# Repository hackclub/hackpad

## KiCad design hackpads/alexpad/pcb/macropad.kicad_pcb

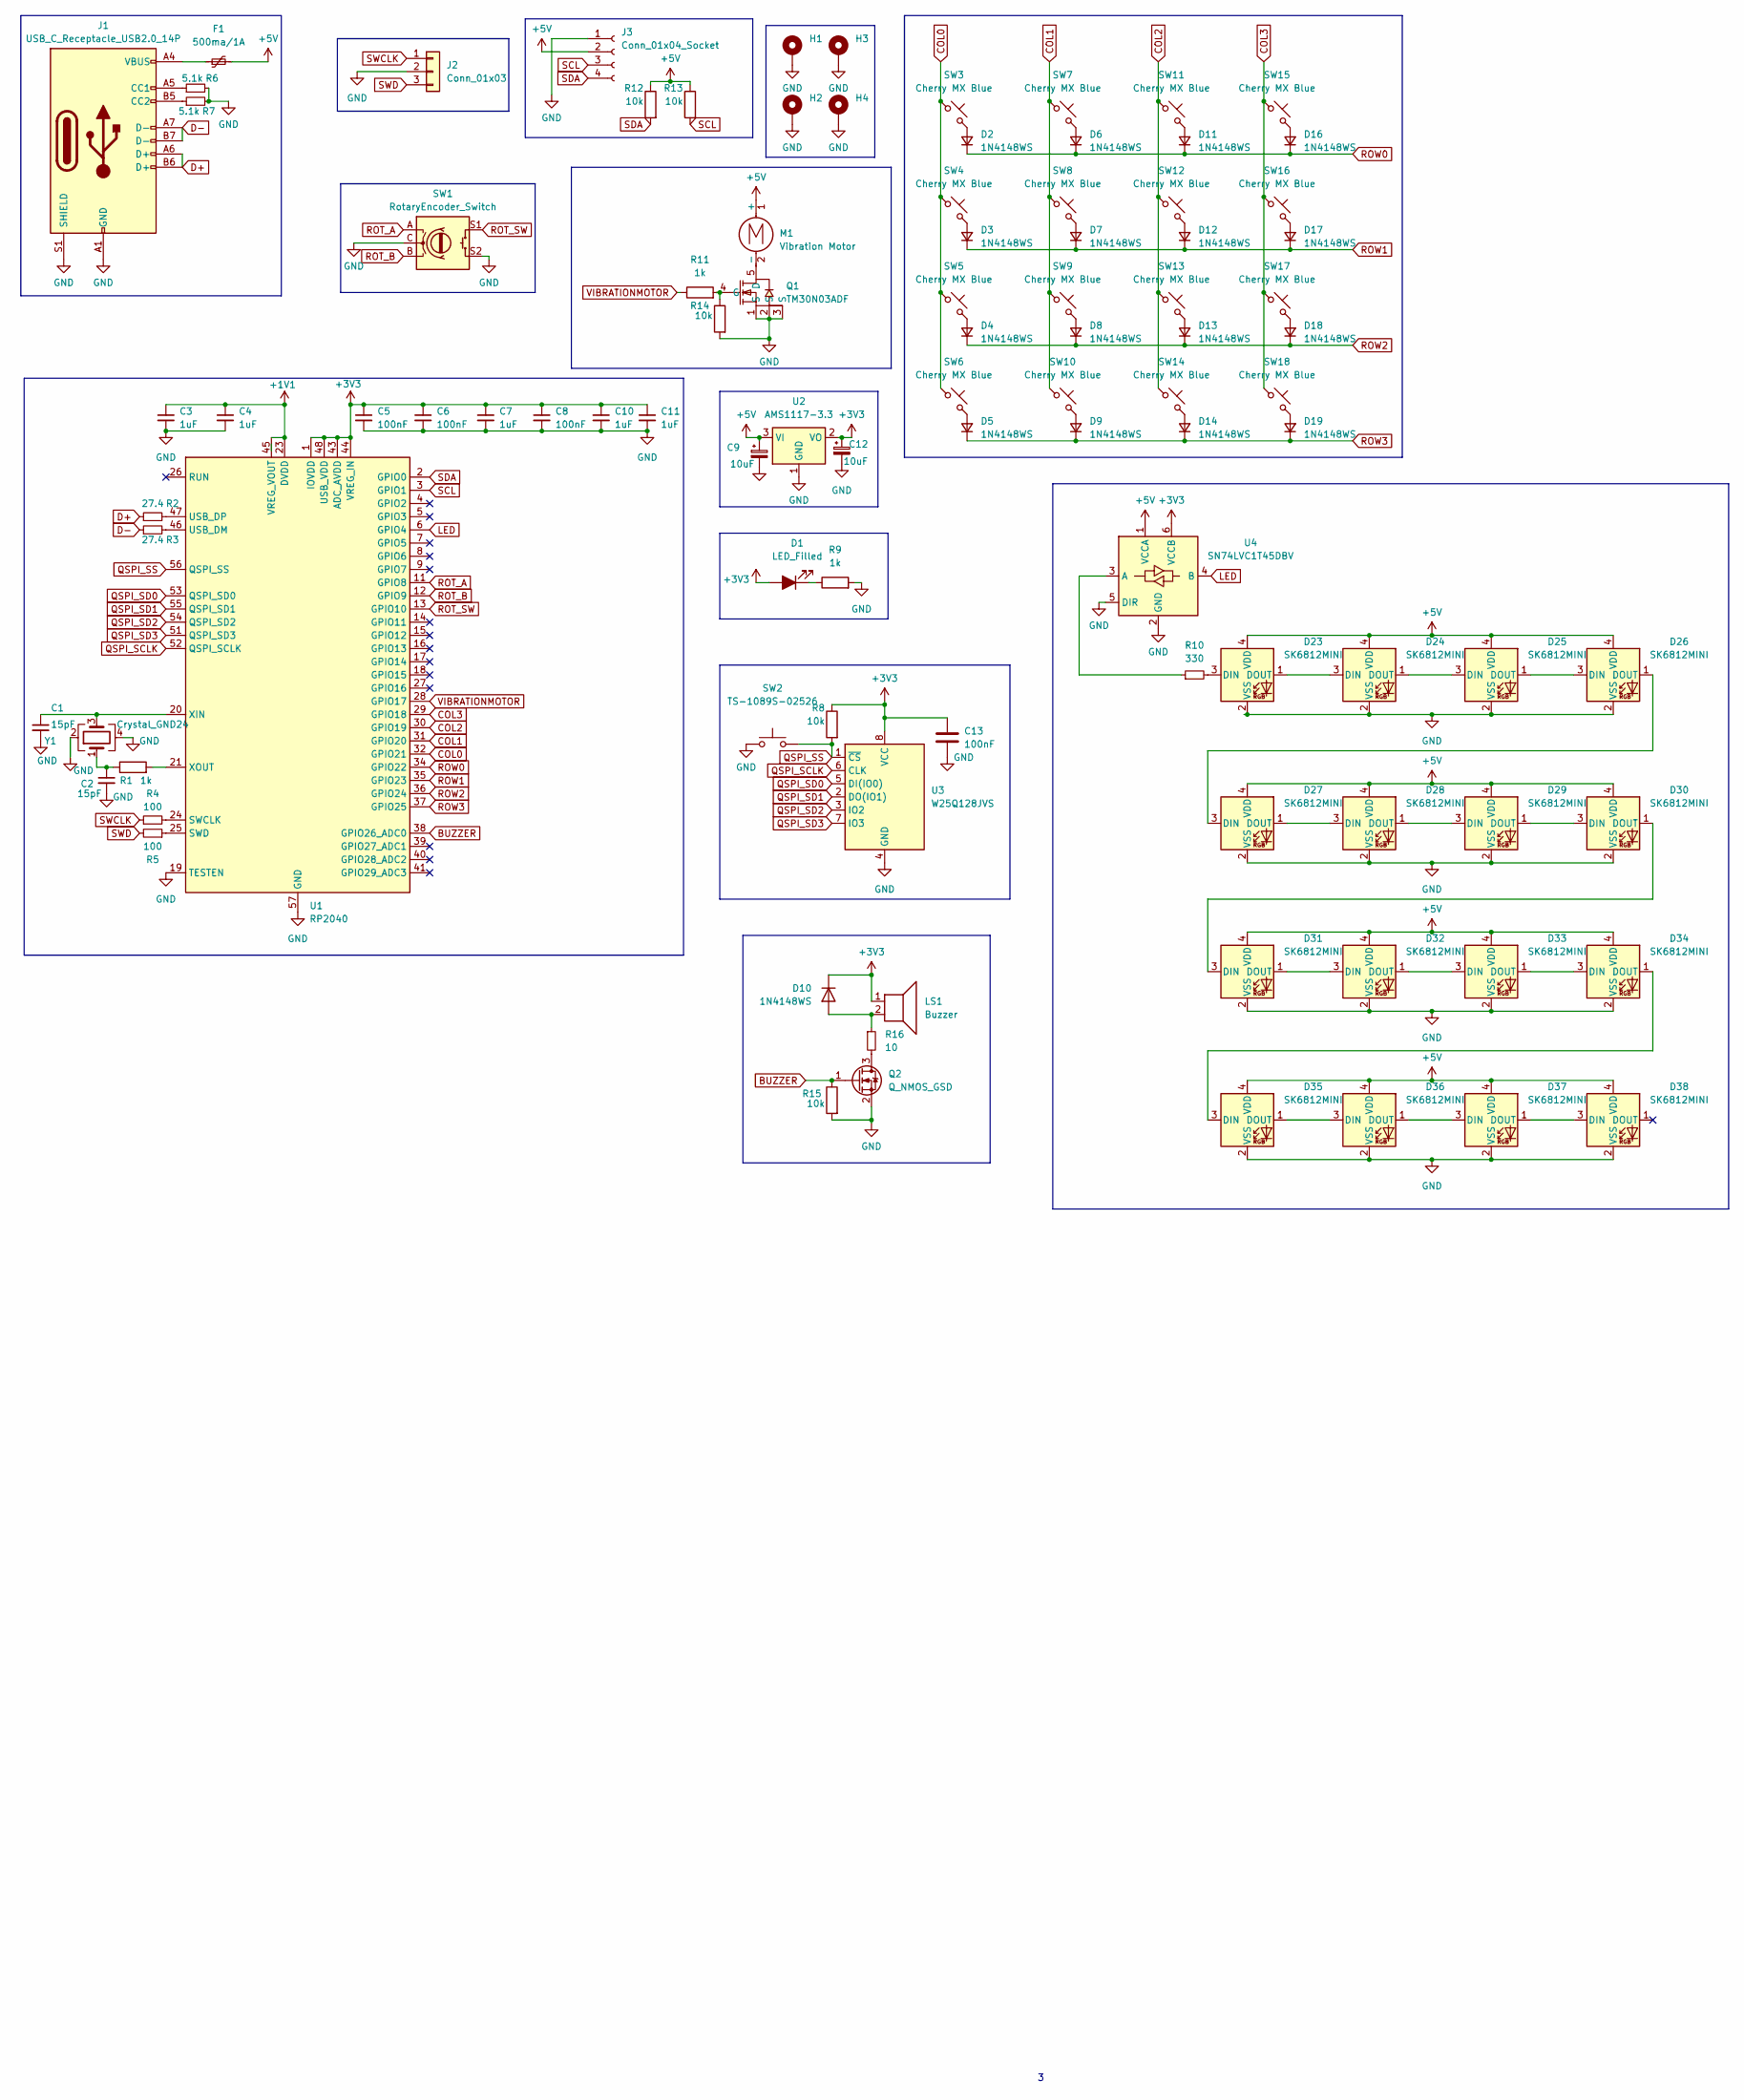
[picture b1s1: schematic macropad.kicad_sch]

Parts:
C1, C2: 15pF; C_0402_1005Metric; LCSC Part C1548
C3, C4, C7, C10, C11: 1uF; C_0402_1005Metric; LCSC Part C52923
C5, C6, C8, C13: 100nF; C_0402_1005Metric; LCSC Part C1525
C9, C12: 10uF; C_1206_3216Metric; LCSC Part C7171
D1: LED_Filled; LED_0603_1608Metric; LCSC Part C2286
D2, D3, D4, D5, D6, D7, D8, D9, D11, D12, D13, D14, D16, D17, D18, D19: 1N4148WS; D_SOD-323F; LCSC Part C917117
D10: 1N4148WS; D_SOD-323; LCSC Part C2828422
D23, D24, D25, D26, D27, D28, D29, D30, D31, D32, D33, D34, D35, D36, D37, D38: SK6812MINI; SK6812MINI-E; LCSC Part C5149201
F1: 500ma/1A; Fuse_1206_3216Metric_Pad1.42x1.75mm_HandSolder; LCSC Part C720075
H1, H2, H3, H4: MountingHole_Pad; MountingHole_2.2mm_M2_DIN965_Pad
J1: USB_C_Receptacle_USB2.0_14P; USB_C_Receptacle_G-Switch_GT-USB-7010ASV; LCSC Part C2988369
J2: Conn_01x03; JST_SH_BM03B-SRSS-TB_1x03-1MP_P1.00mm_Vertical; LCSC Part C160389
J3: Conn_01x04_Socket; OLED-TH_L38.0-W12.0_HS91L02W2C01; LCSC Part C5248081
LS1: Buzzer; BUZ-SMD_4P-L8.5-W8.5-P8.50-BR; LCSC Part C94599
M1: Vibration Motor; PinHeader_1x02_P2.54mm_Vertical
Q1: TM30N03ADF; WDFN-5_L3.3-W3.3-P0.65-BL; LCSC Part C7422839
Q2: Q_NMOS_GSD; SOT-23_Handsoldering; LCSC Part C347475
R1, R9, R11: 1k; R_0402_1005Metric; LCSC Part C11702
R2, R3: 27.4; R_0603_1608Metric; LCSC Part C5126244
R4, R5: 100; R_0603_1608Metric_Pad0.98x0.95mm_HandSolder; LCSC Part C7250
R6, R7: 5.1k; R_0603_1608Metric_Pad0.98x0.95mm_HandSolder; LCSC Part C23186
R8, R12, R13, R14, R15: 10k; R_0805_2012Metric; LCSC Part C17414
R10: 330; R_0603_1608Metric_Pad0.98x0.95mm_HandSolder; LCSC Part C23138
R16: 10; R_0603_1608Metric_Pad0.98x0.95mm_HandSolder; LCSC Part C22859
SW1: RotaryEncoder_Switch; SW-TH_EC11XXXXXXXX; LCSC Part C470742
SW2: TS-1089S-02526; SW-SMD_4P-L4.2-W3.3-P2.15-LS5.1; LCSC Part C455282
SW3, SW4, SW5, SW6, SW7, SW8, SW9, SW10, SW11, SW12, SW13, SW14, SW15, SW16, SW17, SW18: Cherry MX Blue; SW_Cherry_MX_PCB_1.00u
U1: RP2040; QFN-56-1EP_7x7mm_P0.4mm_EP3.2x3.2mm; LCSC Part C2040
U2: AMS1117-3.3; SOT-223-3_TabPin2; LCSC Part C6186
U3: W25Q128JVS; SOIC-8_5.23x5.23mm_P1.27mm; LCSC Part C97521
U4: SN74LVC1T45DBV; SOT-23-6; LCSC Part C7843
Y1: Crystal_GND24; Crystal_SMD_3225-4Pin_3.2x2.5mm; LCSC Part C20625731

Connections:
+1V1: C3.1, C4.1, U1.23 (DVDD), U1.45 (VREG_VOUT), U1.50 (DVDD)
+3V3: C5.1, C6.1, C7.1, C8.1, C10.1, C11.1, C12.1, C13.1, D1.2 (A), D10.1 (K), LS1.1, R8.1, U1.1 (IOVDD), U1.10 (IOVDD), U1.22 (IOVDD), U1.33 (IOVDD), U1.42 (IOVDD), U1.43 (ADC_AVDD), U1.44 (VREG_IN), U1.48 (USB_VDD), U1.49 (IOVDD), U2.2 (VO), U3.8 (VCC), U4.6 (VCCB)
+5V: C9.1, D23.4 (VDD), D24.4 (VDD), D25.4 (VDD), D26.4 (VDD), D27.4 (VDD), D28.4 (VDD), D29.4 (VDD), D30.4 (VDD), D31.4 (VDD), D32.4 (VDD), D33.4 (VDD), D34.4 (VDD), D35.4 (VDD), D36.4 (VDD), D37.4 (VDD), D38.4 (VDD), F1.2, J3.2, M1.1 (+), R12.1, R13.1, U2.3 (VI), U4.1 (VCCA)
BUZZER: Q2.1 (G), R15.1, U1.38 (GPIO26_ADC0)
COL0: SW3.1, SW4.1, SW5.1, SW6.1, U1.32 (GPIO21)
COL1: SW7.1, SW8.1, SW9.1, SW10.1, U1.31 (GPIO20)
COL2: SW11.1, SW12.1, SW13.1, SW14.1, U1.30 (GPIO19)
COL3: SW15.1, SW16.1, SW17.1, SW18.1, U1.29 (GPIO18)
D+: J1.A6 (D+), J1.B6 (D+), R2.1
D-: J1.A7 (D-), J1.B7 (D-), R3.1
GND: C1.2, C2.2, C3.2, C4.2, C5.2, C6.2, C7.2, C8.2, C9.2, C10.2, C11.2, C12.2, C13.2, D23.2 (VSS), D24.2 (VSS), D25.2 (VSS), D26.2 (VSS), D27.2 (VSS), D28.2 (VSS), D29.2 (VSS), D30.2 (VSS), D31.2 (VSS), D32.2 (VSS), D33.2 (VSS), D34.2 (VSS), D35.2 (VSS), D36.2 (VSS), D37.2 (VSS), D38.2 (VSS), H1.1, H2.1, H3.1, H4.1, J1.A1 (GND), J1.A12 (GND), J1.B1 (GND), J1.B12 (GND), J1.S1 (SHIELD), J2.2, J3.1, Q1.1 (S), Q1.2 (S), Q1.3 (S), Q2.2 (S), R6.2, R7.2, R9.2, R14.2, R15.2, SW1.C, SW1.S2, SW2.1, U1.19 (TESTEN), U1.57 (GND), U2.1 (GND), U3.4 (GND), U4.2 (GND), U4.5 (DIR), Y1.2, Y1.4
LED: U1.6 (GPIO4), U4.4 (B)
unnamed: C2.1, R1.1, Y1.1
unnamed: D1.1 (K), R9.1
unnamed: D2.2 (A), SW3.2
unnamed: D3.2 (A), SW4.2
unnamed: D4.2 (A), SW5.2
unnamed: D5.2 (A), SW6.2
unnamed: D6.2 (A), SW7.2
unnamed: D7.2 (A), SW8.2
unnamed: D8.2 (A), SW9.2
unnamed: D9.2 (A), SW10.2
unnamed: D10.2 (A), LS1.2, R16.1
unnamed: D11.2 (A), SW11.2
unnamed: D12.2 (A), SW12.2
unnamed: D13.2 (A), SW13.2
unnamed: D14.2 (A), SW14.2
unnamed: D16.2 (A), SW15.2
unnamed: D17.2 (A), SW16.2
unnamed: D18.2 (A), SW17.2
unnamed: D19.2 (A), SW18.2
unnamed: D23.3 (DIN), R10.2
unnamed: D23.1 (DOUT), D24.3 (DIN)
unnamed: D24.1 (DOUT), D25.3 (DIN)
unnamed: D25.1 (DOUT), D26.3 (DIN)
unnamed: D26.1 (DOUT), D27.3 (DIN)
unnamed: D27.1 (DOUT), D28.3 (DIN)
unnamed: D28.1 (DOUT), D29.3 (DIN)
unnamed: D29.1 (DOUT), D30.3 (DIN)
unnamed: D30.1 (DOUT), D31.3 (DIN)
unnamed: D31.1 (DOUT), D32.3 (DIN)
unnamed: D32.1 (DOUT), D33.3 (DIN)
unnamed: D33.1 (DOUT), D34.3 (DIN)
unnamed: D34.1 (DOUT), D35.3 (DIN)
unnamed: D35.1 (DOUT), D36.3 (DIN)
unnamed: D36.1 (DOUT), D37.3 (DIN)
unnamed: D37.1 (DOUT), D38.3 (DIN)
unnamed: F1.1, J1.A4 (VBUS), J1.A9 (VBUS), J1.B4 (VBUS), J1.B9 (VBUS)
unnamed: J1.A5 (CC1), R6.1
unnamed: J1.B5 (CC2), R7.1
unnamed: M1.2 (-), Q1.5 (D)
unnamed: Q1.4 (G), R11.2, R14.1
unnamed: Q2.3 (D), R16.2
unnamed: R4.2, U1.24 (SWCLK)
unnamed: R5.1, U1.25 (SWD)
unnamed: R3.2, U1.46 (USB_DM)
unnamed: R2.2, U1.47 (USB_DP)
unnamed: C1.1, U1.20 (XIN), Y1.3
unnamed: R1.2, U1.21 (XOUT)
unnamed: R10.1, U4.3 (A)
QSPI_SCLK: U1.52 (QSPI_SCLK), U3.6 (CLK)
QSPI_SD0: U1.53 (QSPI_SD0), U3.5 (DI(IO0))
QSPI_SD1: U1.55 (QSPI_SD1), U3.2 (DO(IO1))
QSPI_SD2: U1.54 (QSPI_SD2), U3.3 (IO2)
QSPI_SD3: U1.51 (QSPI_SD3), U3.7 (IO3)
QSPI_SS: R8.2, SW2.2, U1.56 (QSPI_SS), U3.1 (~CS)
ROT_A: SW1.A, U1.11 (GPIO8)
ROT_B: SW1.B, U1.12 (GPIO9)
ROT_SW: SW1.S1, U1.13 (GPIO10)
ROW0: D2.1 (K), D6.1 (K), D11.1 (K), D16.1 (K), U1.34 (GPIO22)
ROW1: D3.1 (K), D7.1 (K), D12.1 (K), D17.1 (K), U1.35 (GPIO23)
ROW2: D4.1 (K), D8.1 (K), D13.1 (K), D18.1 (K), U1.36 (GPIO24)
ROW3: D5.1 (K), D9.1 (K), D14.1 (K), D19.1 (K), U1.37 (GPIO25)
SCL: J3.3, R13.2, U1.3 (GPIO1)
SDA: J3.4, R12.2, U1.2 (GPIO0)
SWCLK: J2.1, R4.1
SWD: J2.3, R5.2
VIBRATIONMOTOR: R11.1, U1.28 (GPIO17)

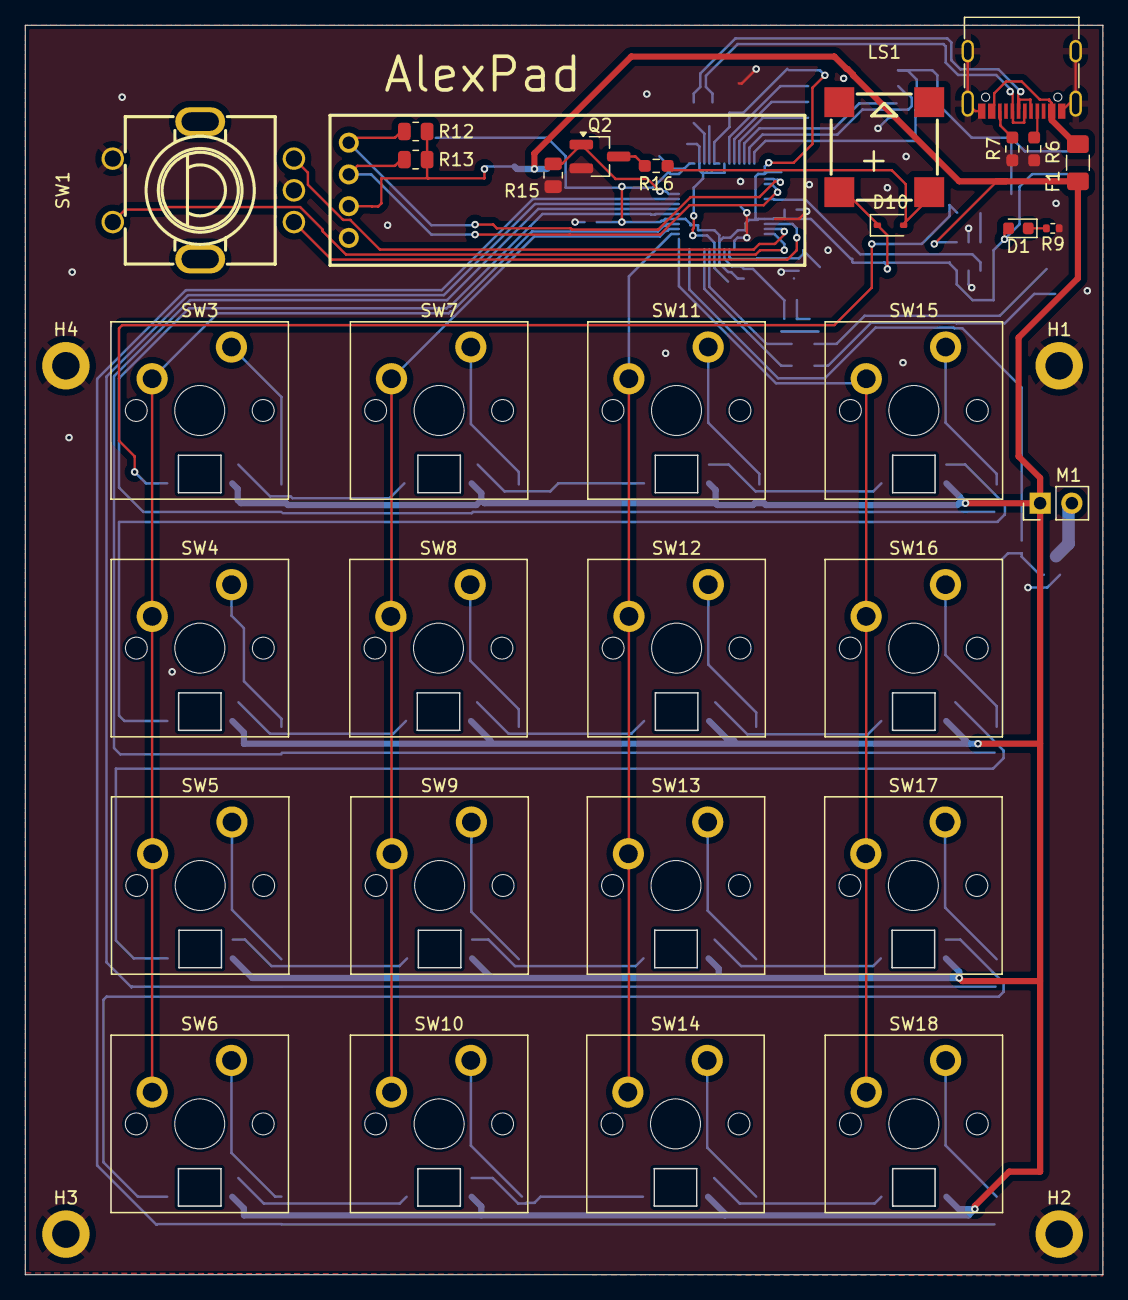
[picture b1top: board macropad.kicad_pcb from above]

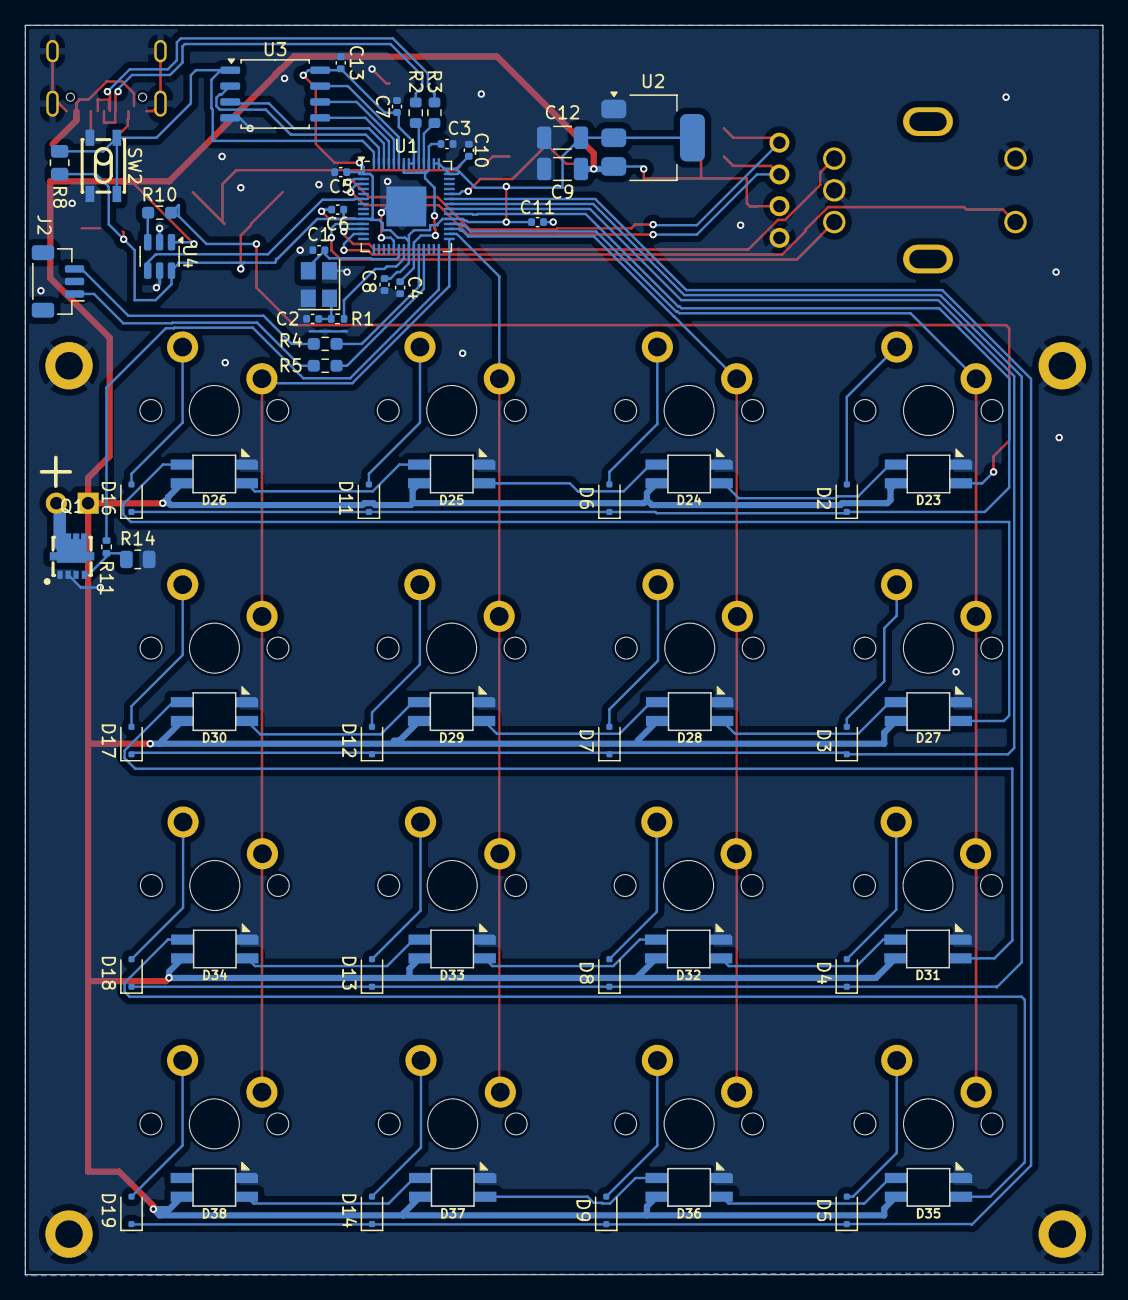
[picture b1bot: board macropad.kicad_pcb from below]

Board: 2 copper layers, 86.2 x 100.0 mm, 98 parts (62 on the bottom side), 78 nets.

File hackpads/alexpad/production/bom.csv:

"Reference","Qty","Value","Footprint","LCSC Part"
"C1,C2","2","15pF","Capacitor_SMD:C_0402_1005Metric","C1548"
"C5,C6,C8,C13","4","100nF","Capacitor_SMD:C_0402_1005Metric","C1525"
"C3,C4,C7,C10,C11","5","1uF","Capacitor_SMD:C_0402_1005Metric","C52923"
"C9,C12","2","10uF","Capacitor_SMD:C_1206_3216Metric","C7171"
"R2,R3","2","27.4","Resistor_SMD:R_0603_1608Metric","C5126244"
"R4,R5","2","100","Resistor_SMD:R_0603_1608Metric_Pad0.98x0.95mm_HandSolder"," C7250"
"R10","1","330","Resistor_SMD:R_0603_1608Metric_Pad0.98x0.95mm_HandSolder","C23138"
"R1,R9,R11","3","1k","Resistor_SMD:R_0402_1005Metric","C11702"
"R6,R7","2","5.1k","Resistor_SMD:R_0603_1608Metric_Pad0.98x0.95mm_HandSolder","C23186"
"R8,R12,R13,R14","4","10k","Resistor_SMD:R_0805_2012Metric"," C17414"
"D2,D3,D4,D5,D6,D7,D8,D9,D11,D12,D13,D14,D16,D17,D18,D19","16","1N4148WS","Diode_SMD:D_SOD-323F","C917117"
"F1","1","500ma/1A","Fuse:Fuse_1206_3216Metric_Pad1.42x1.75mm_HandSolder","C720075"
"U2","1","AMS1117-3.3","Package_TO_SOT_SMD:SOT-223-3_TabPin2","C6186"
"SW3,SW4,SW5,SW6,SW7,SW8,SW9,SW10,SW11,SW12,SW13,SW14,SW15,SW16,SW17,SW18","16","Cherry MX Blue","PCM_Switch_Keyboard_Cherry_MX:SW_Cherry_MX_PCB_1.00u",""
"J2","1","Conn_01x03","Connector_JST:JST_SH_BM03B-SRSS-TB_1x03-1MP_P1.00mm_Vertical","C160389"
"J3","1","Conn_01x04_Socket","easyeda2kicad:OLED-TH_L38.0-W12.0_HS91L02W2C01","C5248081"
"Y1","1","Crystal_GND24","Crystal:Crystal_SMD_3225-4Pin_3.2x2.5mm","C20625731"
"D1","1","LED_Filled","LED_SMD:LED_0603_1608Metric","C2286"
"H1,H2,H3,H4","4","MountingHole_Pad","MountingHole:MountingHole_2.2mm_M2_DIN965_Pad",""
"SW1","1","RotaryEncoder_Switch","easyeda2kicad:SW-TH_EC11XXXXXXXX","C470742"
"U1","1","RP2040","Package_DFN_QFN:QFN-56-1EP_7x7mm_P0.4mm_EP3.2x3.2mm","C2040"
"D23,D24,D25,D26,D27,D28,D29,D30,D31,D32,D33,D34,D35,D36,D37,D38","16","SK6812MINI","cheyao macropad main PCB-third_party_neopixel.petty:SK6812MINI-E","C5149201"
"U4","1","SN74LVC1T45DBV","Package_TO_SOT_SMD:SOT-23-6","C7843"
"Q1","1","TM30N03ADF","easyeda2kicad:WDFN-5_L3.3-W3.3-P0.65-BL","C7422839"
"SW2","1","TS-1089S-02526","easyeda2kicad:SW-SMD_4P-L4.2-W3.3-P2.15-LS5.1","C455282"
"J1","1","USB_C_Receptacle_USB2.0_14P","Connector_USB:USB_C_Receptacle_G-Switch_GT-USB-7010ASV","C2988369"
"M1","1","Vibration Motor","Connector_PinHeader_2.54mm:PinHeader_1x02_P2.54mm_Vertical",""
"U3","1","W25Q128JVS","Package_SO:SOIC-8_5.23x5.23mm_P1.27mm","C97521"

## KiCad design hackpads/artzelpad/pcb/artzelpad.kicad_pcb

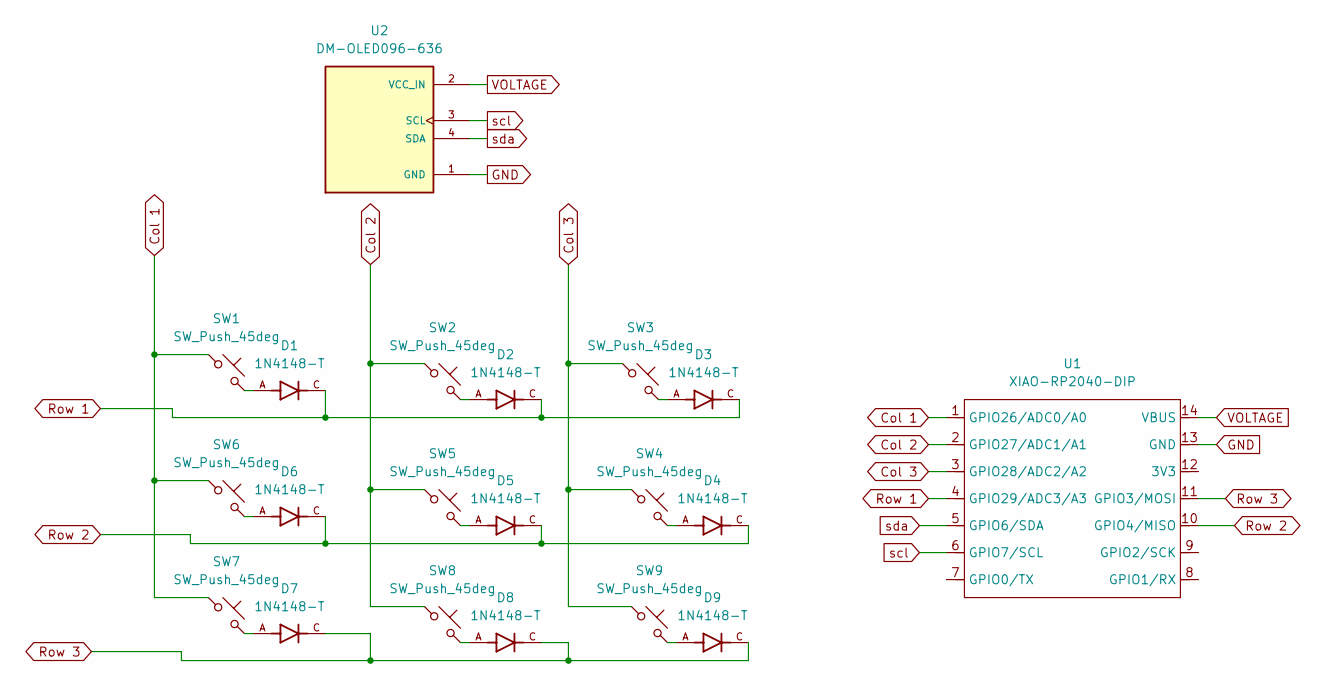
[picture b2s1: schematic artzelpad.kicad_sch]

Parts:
D1, D2, D3, D4, D5, D6, D7, D8, D9: 1N4148-T; DIOAD820W60L400D200; PARTREV 9-3
SW1, SW2, SW3, SW4, SW5, SW6, SW7, SW8, SW9: SW_Push_45deg; SW_Cherry_MX_1.00u_PCB_3D_model
U1: XIAO-RP2040-DIP; XIAO-RP2040-DIP_1
U2: DM-OLED096-636; SSD1306-0.91-OLED-4pin-128x32; PARTREV 2018-09-10

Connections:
Col 1: SW1.1, SW6.1, SW7.1, U1.1 (GPIO26/ADC0/A0)
Col 2: SW2.1, SW5.1, SW8.1, U1.2 (GPIO27/ADC1/A1)
Col 3: SW3.1, SW4.1, SW9.1, U1.3 (GPIO28/ADC2/A2)
GND: U1.13 (GND), U2.1 (GND)
unnamed: D1.A, SW1.2
unnamed: D2.A, SW2.2
unnamed: D3.A, SW3.2
unnamed: D4.A, SW4.2
unnamed: D5.A, SW5.2
unnamed: D6.A, SW6.2
unnamed: D7.A, SW7.2
unnamed: D8.A, SW8.2
unnamed: D9.A, SW9.2
Row 1: D1.C, D2.C, D3.C, U1.4 (GPIO29/ADC3/A3)
Row 2: D4.C, D5.C, D6.C, U1.10 (GPIO4/MISO)
Row 3: D7.C, D8.C, D9.C, U1.11 (GPIO3/MOSI)
VOLTAGE: U1.14 (VBUS), U2.2 (VCC_IN)
scl: U1.6 (GPIO7/SCL), U2.3 (SCL)
sda: U1.5 (GPIO6/SDA), U2.4 (SDA)

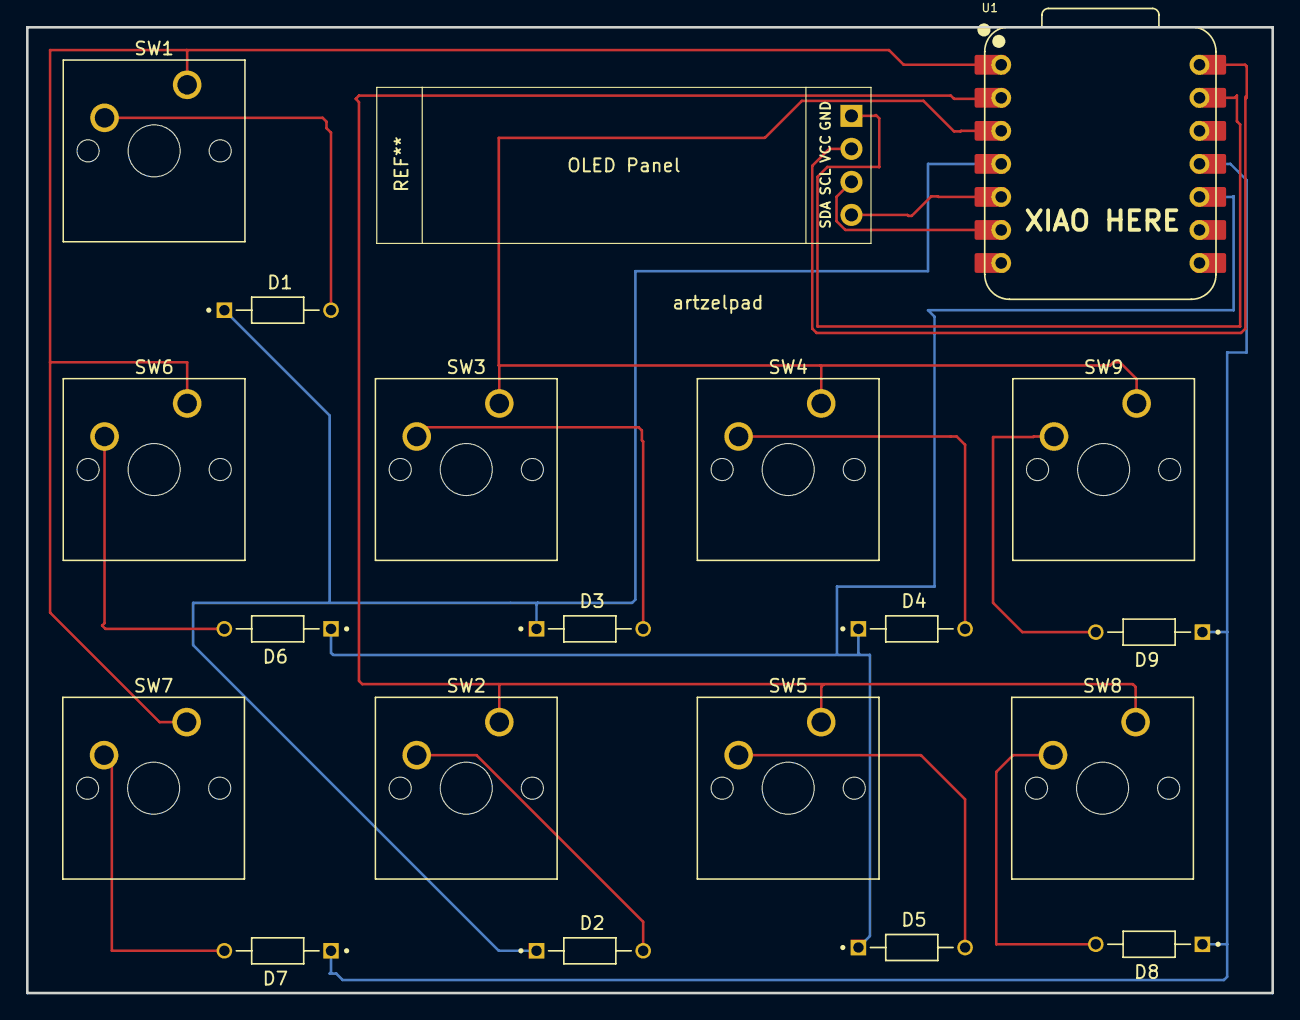
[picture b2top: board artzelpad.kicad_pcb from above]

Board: 2 copper layers, 95.8 x 74.2 mm, 19 parts (0 on the bottom side), 15 nets.

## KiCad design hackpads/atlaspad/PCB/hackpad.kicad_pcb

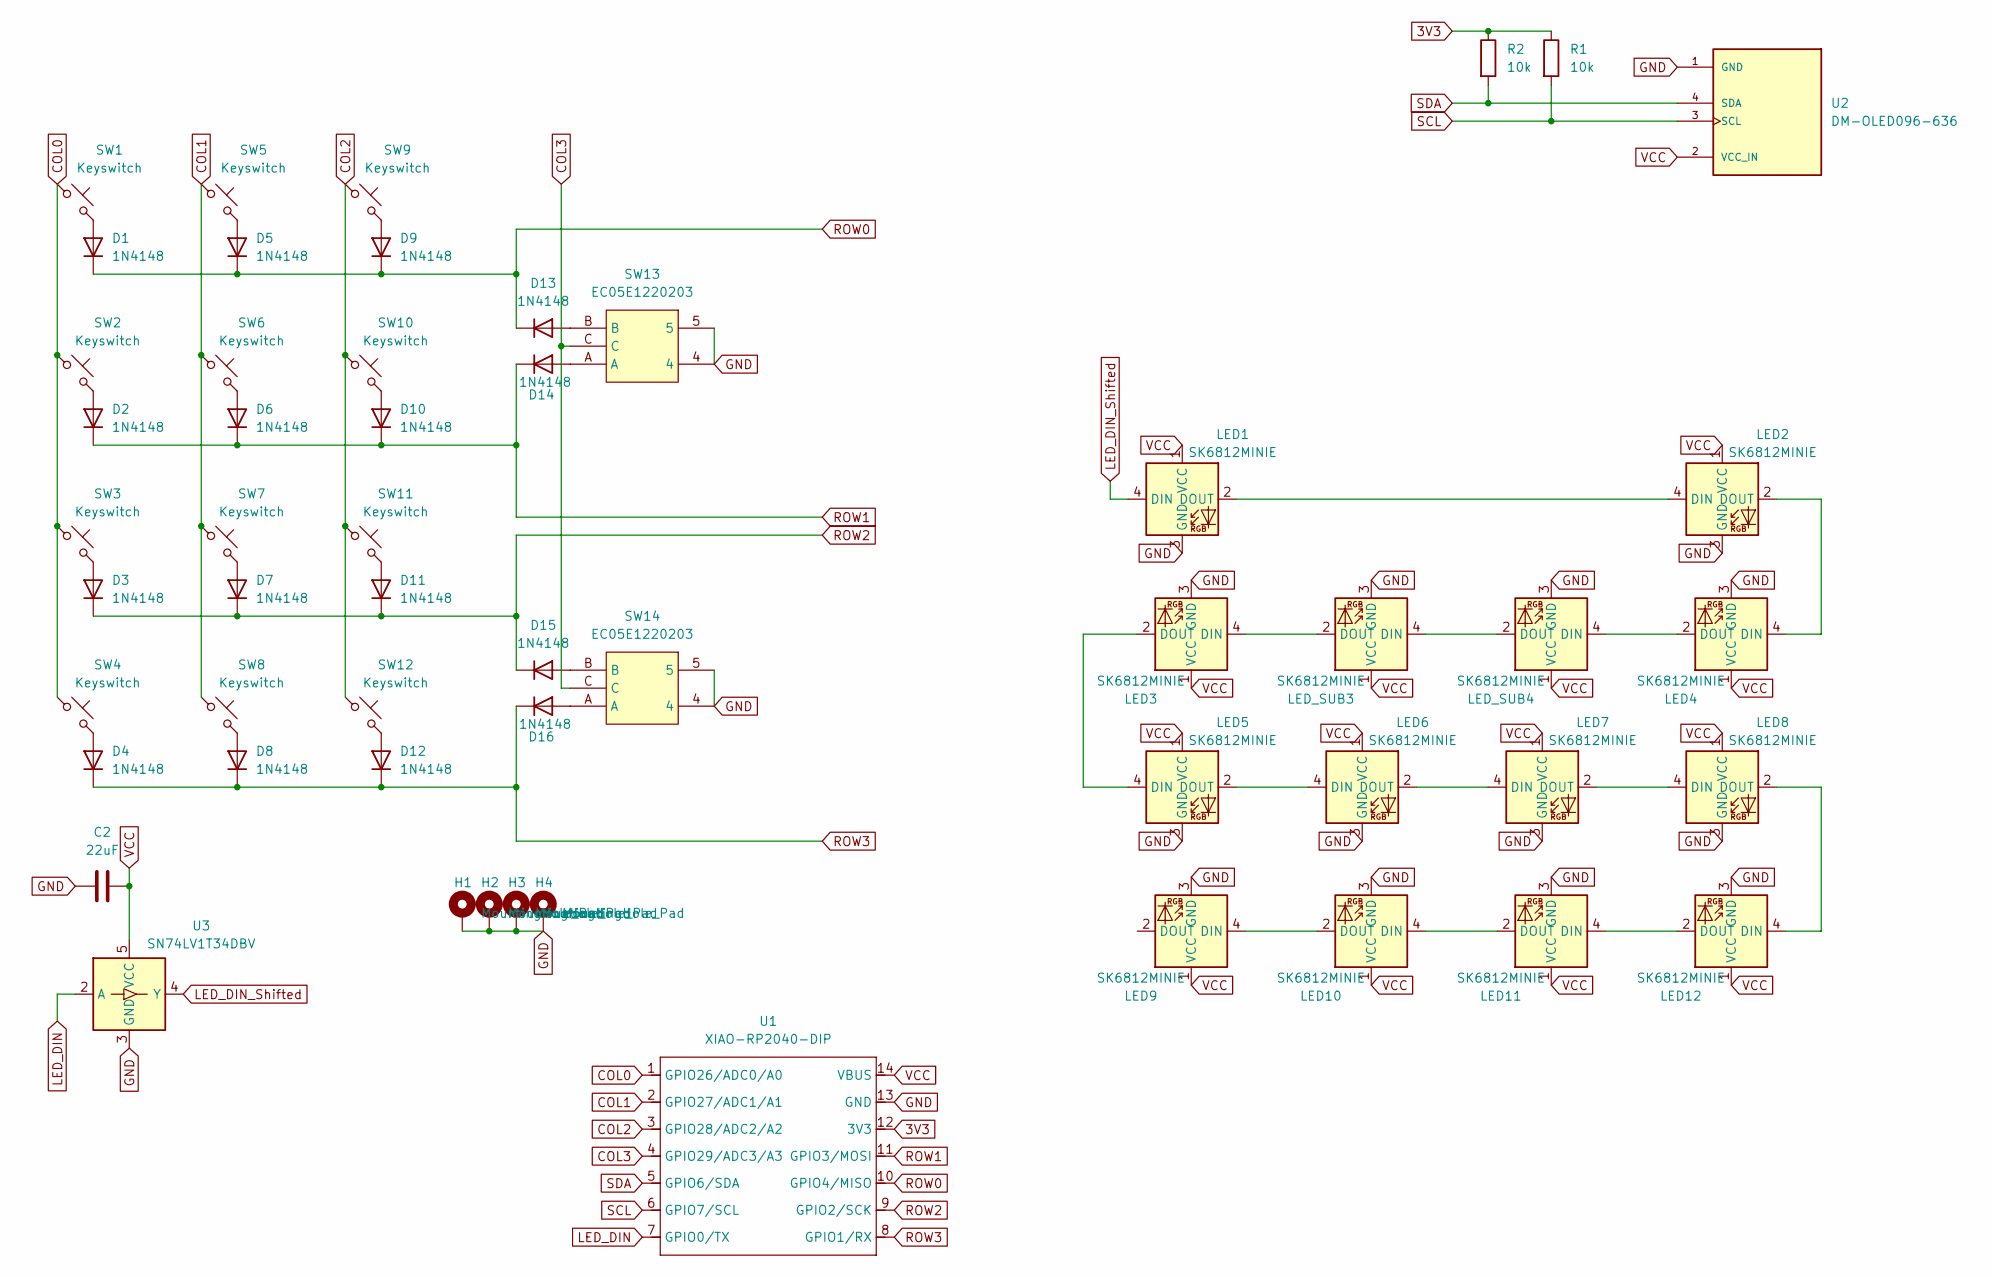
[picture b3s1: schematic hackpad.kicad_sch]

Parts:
C2: 22uF; C_Radial_D5.0mm_H7.0mm_P2.00mm
D1, D2, D3, D4, D5, D6, D7, D8, D9, D10, D11, D12, D13, D14, D15, D16: 1N4148; D_DO-35_SOD27_P7.62mm_Horizontal
H1, H2, H3, H4: MountingHole_Pad; MountingHole_2.2mm_M2_DIN965_Pad
LED1, LED2, LED3, LED4, LED5, LED6, LED7, LED8, LED9, LED10, LED11, LED12: SK6812MINIE; SK6812MINI-E-Reverse
LED_SUB3, LED_SUB4: SK6812MINIE; SK6812MINI-E-Reverse
R1, R2: 10k; R_0402_1005Metric_Pad0.72x0.64mm_HandSolder
SW1, SW2, SW3, SW4, SW5, SW6, SW7, SW8, SW9, SW10, SW11, SW12: Keyswitch; Kailh-PG1353-Solderable-1U
SW13, SW14: EC05E1220203; SW-SMD_EC05E1220203; LCSC Part C390930
U1: XIAO-RP2040-DIP
U2: DM-OLED096-636; MODULE_DM-OLED096-636; PARTREV 2018-09-10
U3: SN74LV1T34DBV; SOT-23-5

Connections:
3V3: R1.1, R2.1, U1.12 (3V3)
COL0: SW1.1, SW2.1, SW3.1, SW4.1, U1.1 (GPIO26/ADC0/A0)
COL1: SW5.1, SW6.1, SW7.1, SW8.1, U1.2 (GPIO27/ADC1/A1)
COL2: SW9.1, SW10.1, SW11.1, SW12.1, U1.3 (GPIO28/ADC2/A2)
COL3: SW13.C, SW14.C, U1.4 (GPIO29/ADC3/A3)
GND: C2.1, H1.1, H2.1, H3.1, H4.1, LED1.3 (GND), LED2.3 (GND), LED3.3 (GND), LED4.3 (GND), LED5.3 (GND), LED6.3 (GND), LED7.3 (GND), LED8.3 (GND), LED9.3 (GND), LED10.3 (GND), LED11.3 (GND), LED12.3 (GND), LED_SUB3.3 (GND), LED_SUB4.3 (GND), SW13.4, SW13.5, SW14.4, SW14.5, U1.13 (GND), U2.1 (GND), U3.3 (GND)
LED_DIN: U1.7 (GPIO0/TX), U3.2 (A)
LED_DIN_Shifted: LED1.4 (DIN), U3.4 (Y)
unnamed: D1.2 (A), SW1.2
unnamed: D2.2 (A), SW2.2
unnamed: D3.2 (A), SW3.2
unnamed: D4.2 (A), SW4.2
unnamed: D5.2 (A), SW5.2
unnamed: D6.2 (A), SW6.2
unnamed: D7.2 (A), SW7.2
unnamed: D8.2 (A), SW8.2
unnamed: D9.2 (A), SW9.2
unnamed: D10.2 (A), SW10.2
unnamed: D11.2 (A), SW11.2
unnamed: D12.2 (A), SW12.2
unnamed: D13.2 (A), SW13.B
unnamed: D14.2 (A), SW13.A
unnamed: D15.2 (A), SW14.B
unnamed: D16.2 (A), SW14.A
unnamed: LED1.2 (DOUT), LED2.4 (DIN)
unnamed: LED2.2 (DOUT), LED4.4 (DIN)
unnamed: LED3.4 (DIN), LED_SUB3.2 (DOUT)
unnamed: LED3.2 (DOUT), LED5.4 (DIN)
unnamed: LED4.2 (DOUT), LED_SUB4.4 (DIN)
unnamed: LED5.2 (DOUT), LED6.4 (DIN)
unnamed: LED6.2 (DOUT), LED7.4 (DIN)
unnamed: LED7.2 (DOUT), LED8.4 (DIN)
unnamed: LED10.4 (DIN), LED11.2 (DOUT)
unnamed: LED9.4 (DIN), LED10.2 (DOUT)
unnamed: LED11.4 (DIN), LED12.2 (DOUT)
unnamed: LED8.2 (DOUT), LED12.4 (DIN)
unnamed: LED_SUB3.4 (DIN), LED_SUB4.2 (DOUT)
ROW0: D1.1 (K), D5.1 (K), D9.1 (K), D13.1 (K), U1.10 (GPIO4/MISO)
ROW1: D2.1 (K), D6.1 (K), D10.1 (K), D14.1 (K), U1.11 (GPIO3/MOSI)
ROW2: D3.1 (K), D7.1 (K), D11.1 (K), D15.1 (K), U1.9 (GPIO2/SCK)
ROW3: D4.1 (K), D8.1 (K), D12.1 (K), D16.1 (K), U1.8 (GPIO1/RX)
SCL: R1.2, U1.6 (GPIO7/SCL), U2.3 (SCL)
SDA: R2.2, U1.5 (GPIO6/SDA), U2.4 (SDA)
VCC: C2.2, LED1.1 (VCC), LED2.1 (VCC), LED3.1 (VCC), LED4.1 (VCC), LED5.1 (VCC), LED6.1 (VCC), LED7.1 (VCC), LED8.1 (VCC), LED9.1 (VCC), LED10.1 (VCC), LED11.1 (VCC), LED12.1 (VCC), LED_SUB3.1 (VCC), LED_SUB4.1 (VCC), U1.14 (VBUS), U2.2 (VCC_IN), U3.5 (VCC)

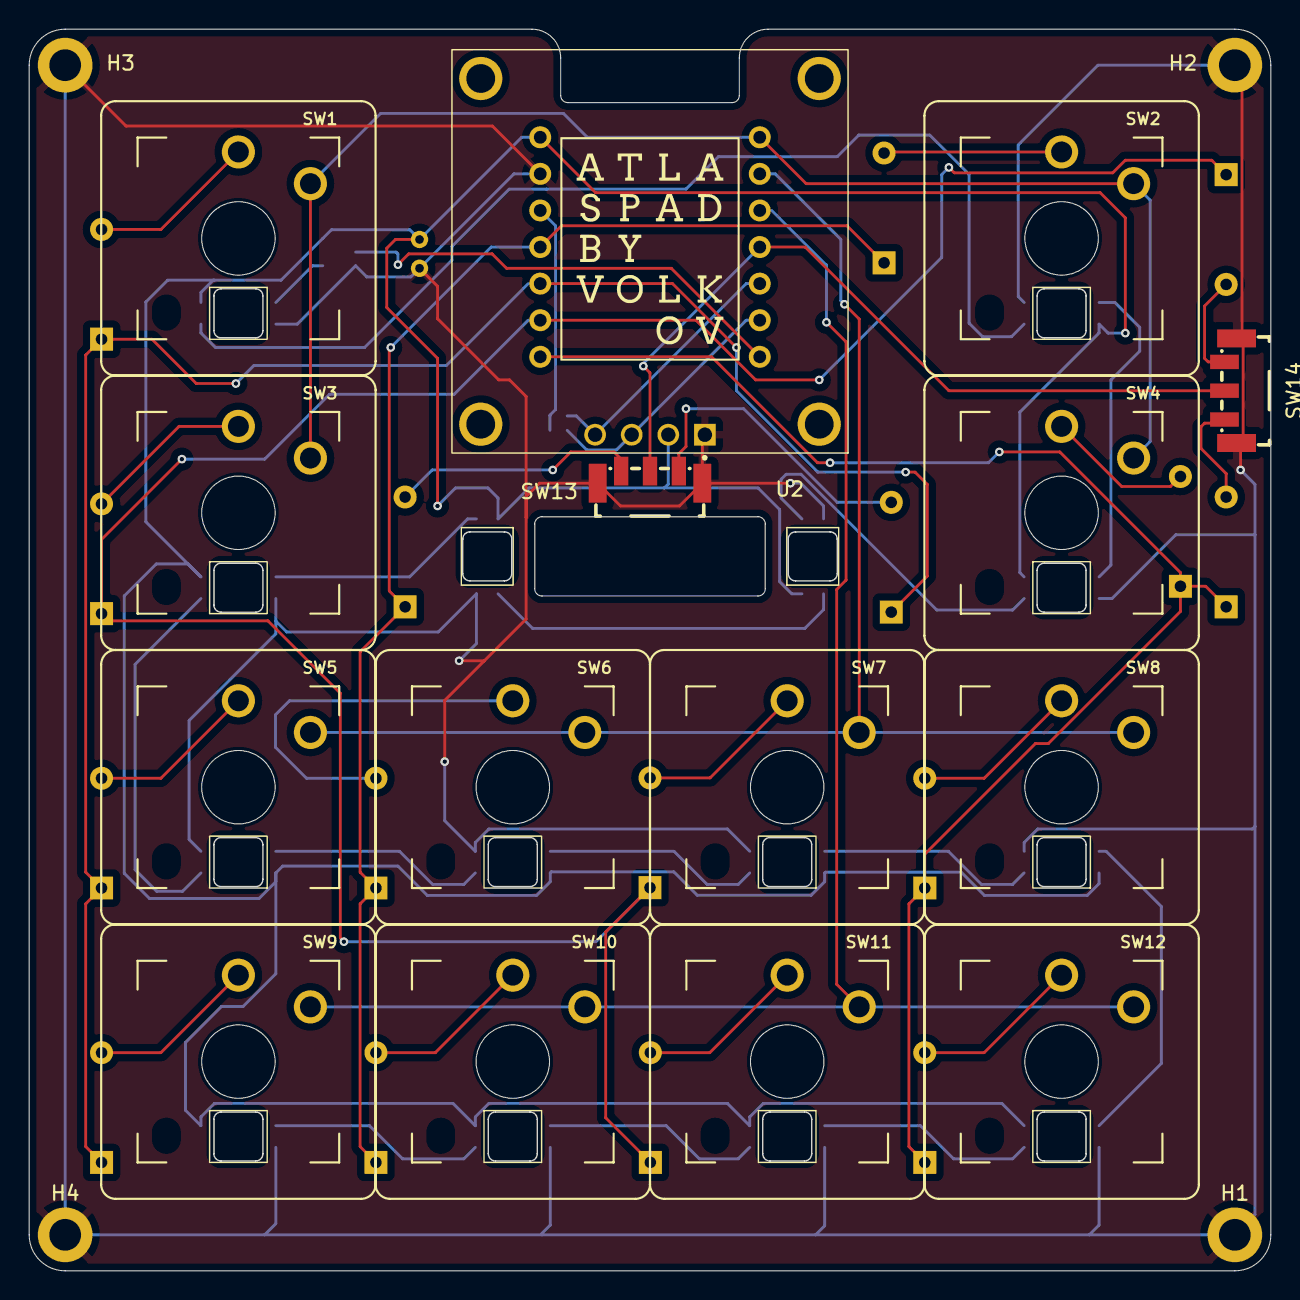
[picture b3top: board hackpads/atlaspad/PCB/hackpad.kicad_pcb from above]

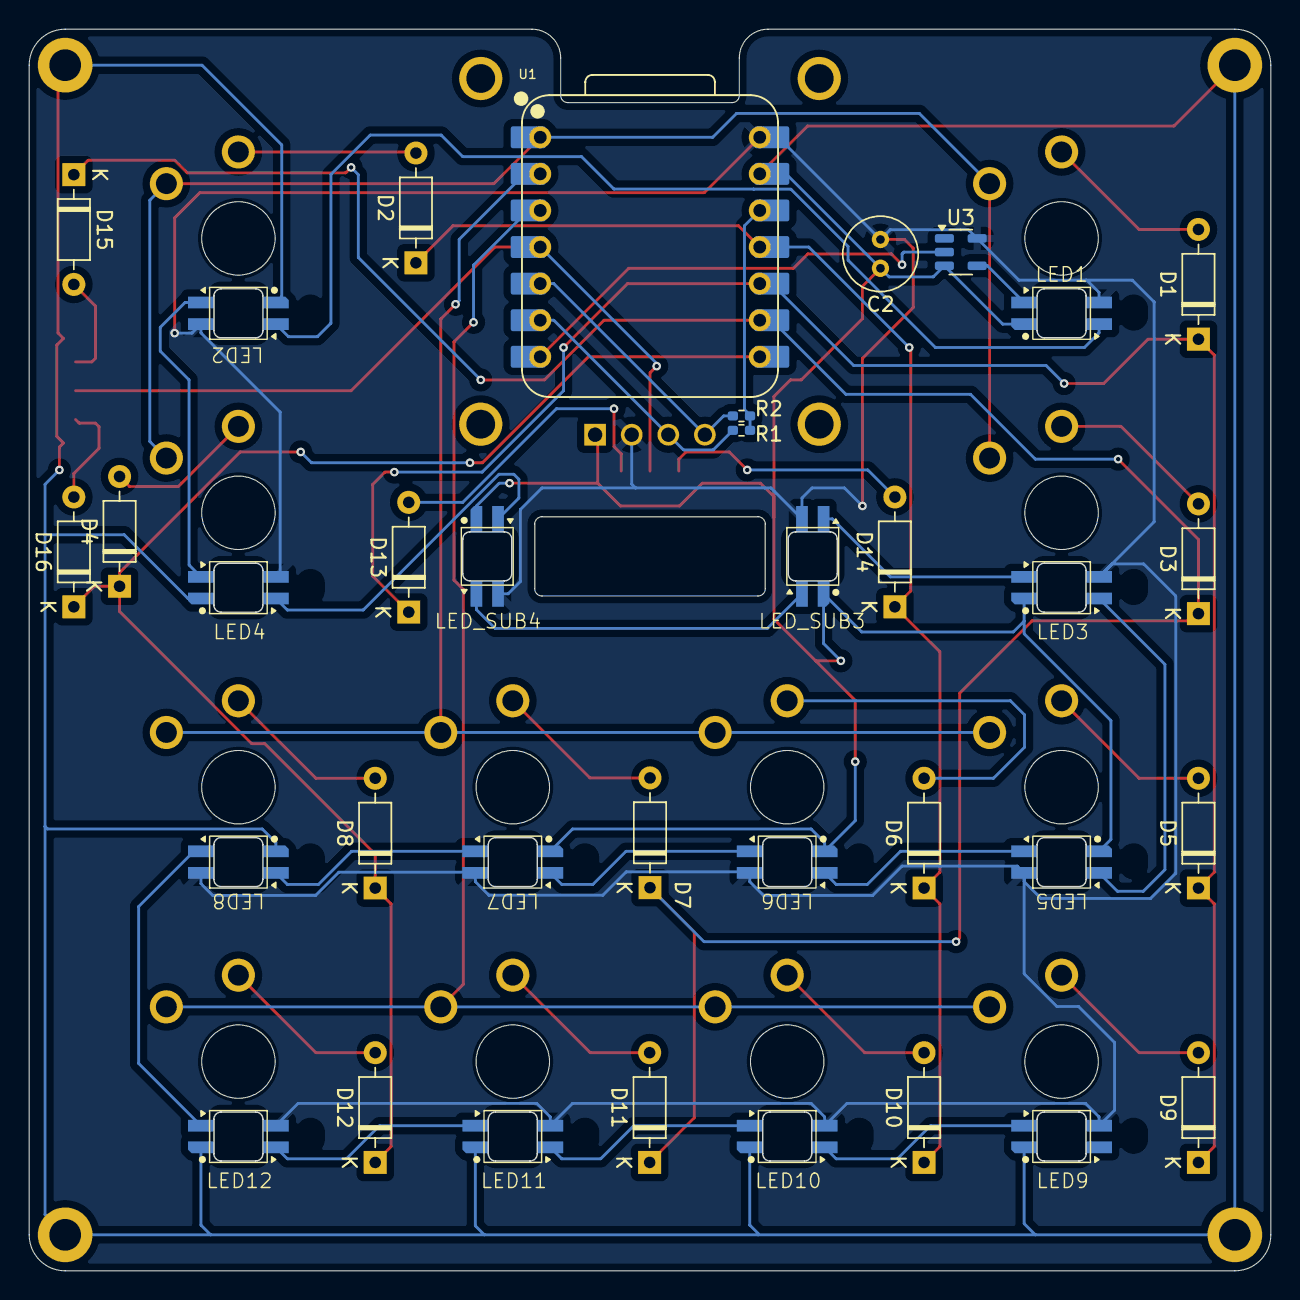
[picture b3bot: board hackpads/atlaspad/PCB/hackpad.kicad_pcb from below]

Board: 2 copper layers, 86.2 x 86.2 mm, 54 parts (21 on the bottom side), 44 nets.
